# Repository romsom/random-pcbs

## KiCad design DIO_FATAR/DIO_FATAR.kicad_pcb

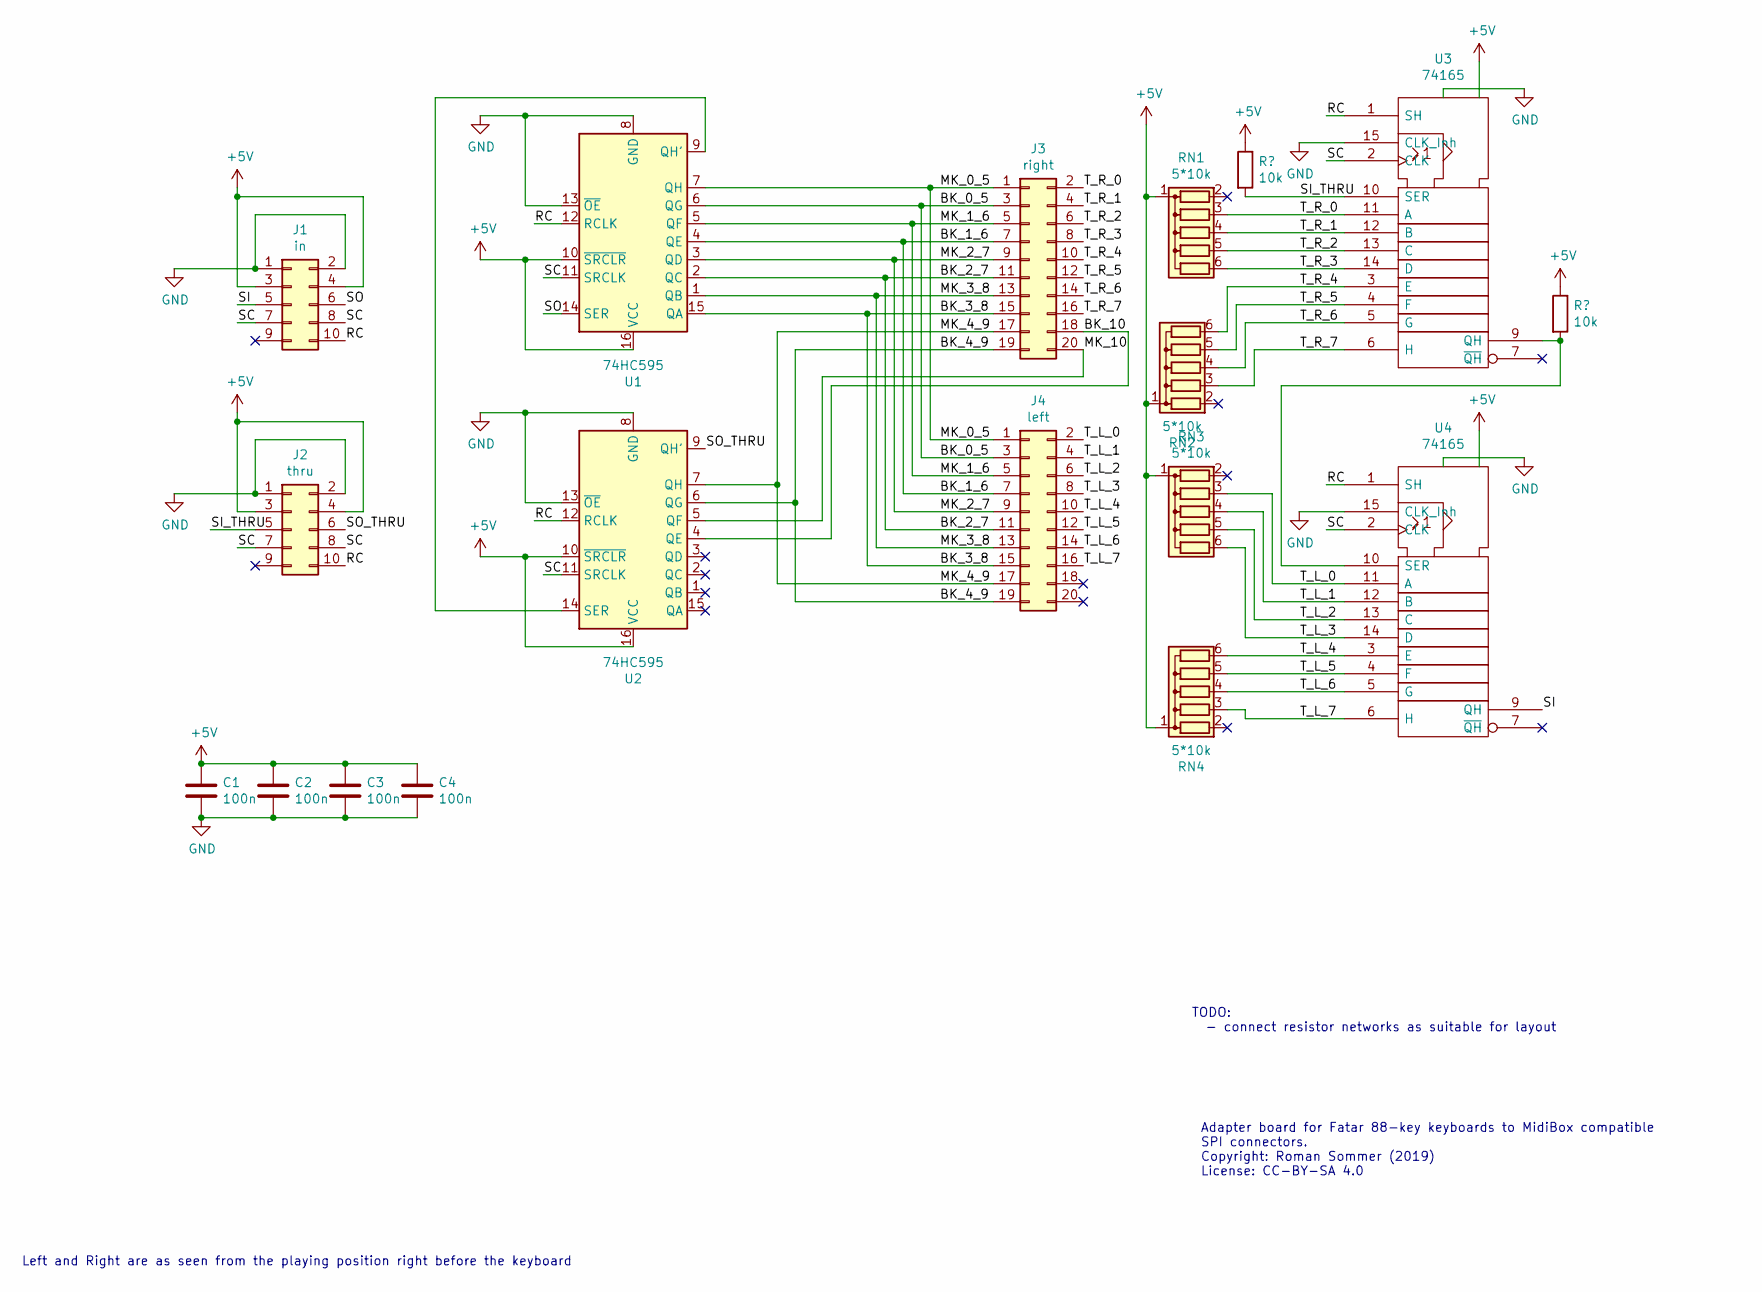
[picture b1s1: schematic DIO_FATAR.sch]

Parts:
C1, C2, C3, C4: 100n; C_Disc_D5.1mm_W3.2mm_P5.00mm
J1: in; IDC-Header_2x05_P2.54mm_Vertical
J2: thru; IDC-Header_2x05_P2.54mm_Vertical
J3: right; IDC-Header_2x10_P2.54mm_Vertical
J4: left; IDC-Header_2x10_P2.54mm_Vertical
RN1, RN2, RN3, RN4: 5*10k; R_Array_SIP6
U1, U2: 74HC595; DIP-16_W7.62mm_LongPads
U3, U4: 74165; DIP-16_W7.62mm_LongPads

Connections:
+5V: C1.1, C2.1, C3.1, C4.1, J1.3, J1.4, J2.3, J2.4, RN1.1 (common), RN2.1 (common), RN3.1 (common), RN4.1 (common), U1.10 (~SRCLR), U1.16 (VCC), U2.10 (~SRCLR), U2.16 (VCC), U3.16 (VCC), U4.16 (VCC); also elsewhere on the board
/BK_0_5: J3.3, J4.3, U1.6 (QG)
/BK_1_6: J3.7, J4.7, U1.4 (QE)
/BK_2_7: J3.11, J4.11, U1.2 (QC)
/BK_3_8: J3.15, J4.15, U1.15 (QA)
/BK_4_9: J3.19, J4.19, U2.6 (QG)
/BK_10: J3.18, U2.4 (QE)
/MK_0_5: J3.1, J4.1, U1.7 (QH)
/MK_1_6: J3.5, J4.5, U1.5 (QF)
/MK_2_7: J3.9, J4.9, U1.3 (QD)
/MK_3_8: J3.13, J4.13, U1.1 (QB)
/MK_4_9: J3.17, J4.17, U2.7 (QH)
/MK_10: J3.20, U2.5 (QF)
/RC: J1.10, J2.10, U1.12 (RCLK), U2.12 (RCLK), U3.1 (SH), U4.1 (SH)
/SC: J1.7, J1.8, J2.7, J2.8, U1.11 (SRCLK), U2.11 (SRCLK), U3.2 (CLK), U4.2 (CLK)
/SI: J1.5, U4.9 (QH)
/SI_THRU: J2.5, U3.10 (SER); also elsewhere on the board
/SO: J1.6, U1.14 (SER)
/SO_THRU: J2.6, U2.9 (QH')
/T_L_0: J4.2, RN3.3 (R2), U4.11 (A)
/T_L_1: J4.4, RN3.4 (R3), U4.12 (B)
/T_L_2: J4.6, RN3.5 (R4), U4.13 (C)
/T_L_3: J4.8, RN3.6 (R5), U4.14 (D)
/T_L_4: J4.10, RN4.6 (R5), U4.3 (E)
/T_L_5: J4.12, RN4.5 (R4), U4.4 (F)
/T_L_6: J4.14, RN4.4 (R3), U4.5 (G)
/T_L_7: J4.16, RN4.3 (R2), U4.6 (H)
/T_R_0: J3.2, RN1.3 (R2), U3.11 (A)
/T_R_1: J3.4, RN1.4 (R3), U3.12 (B)
/T_R_2: J3.6, RN1.5 (R4), U3.13 (C)
/T_R_3: J3.8, RN1.6 (R5), U3.14 (D)
/T_R_4: J3.10, RN2.6 (R5), U3.3 (E)
/T_R_5: J3.12, RN2.5 (R4), U3.4 (F)
/T_R_6: J3.14, RN2.4 (R3), U3.5 (G)
/T_R_7: J3.16, RN2.3 (R2), U3.6 (H)
GND: C1.2, C2.2, C3.2, C4.2, J1.1, J1.2, J2.1, J2.2, U1.8 (GND), U1.13 (~OE), U2.8 (GND), U2.13 (~OE), U3.8 (GND), U3.15 (CLK_Inh), U4.8 (GND), U4.15 (CLK_Inh)
unnamed 40: U3.9 (QH), U4.10 (SER); also elsewhere on the board
unnamed: U1.9 (QH'), U2.14 (SER)

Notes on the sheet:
Left and Right are as seen from the playing position right before the keyboard
Adapter board for Fatar 88-key keyboards to MidiBox compatible SPI connectors. Copyright: Roman Sommer (2019) License: CC-BY-SA 4.0
TODO: - connect resistor networks as suitable for layout

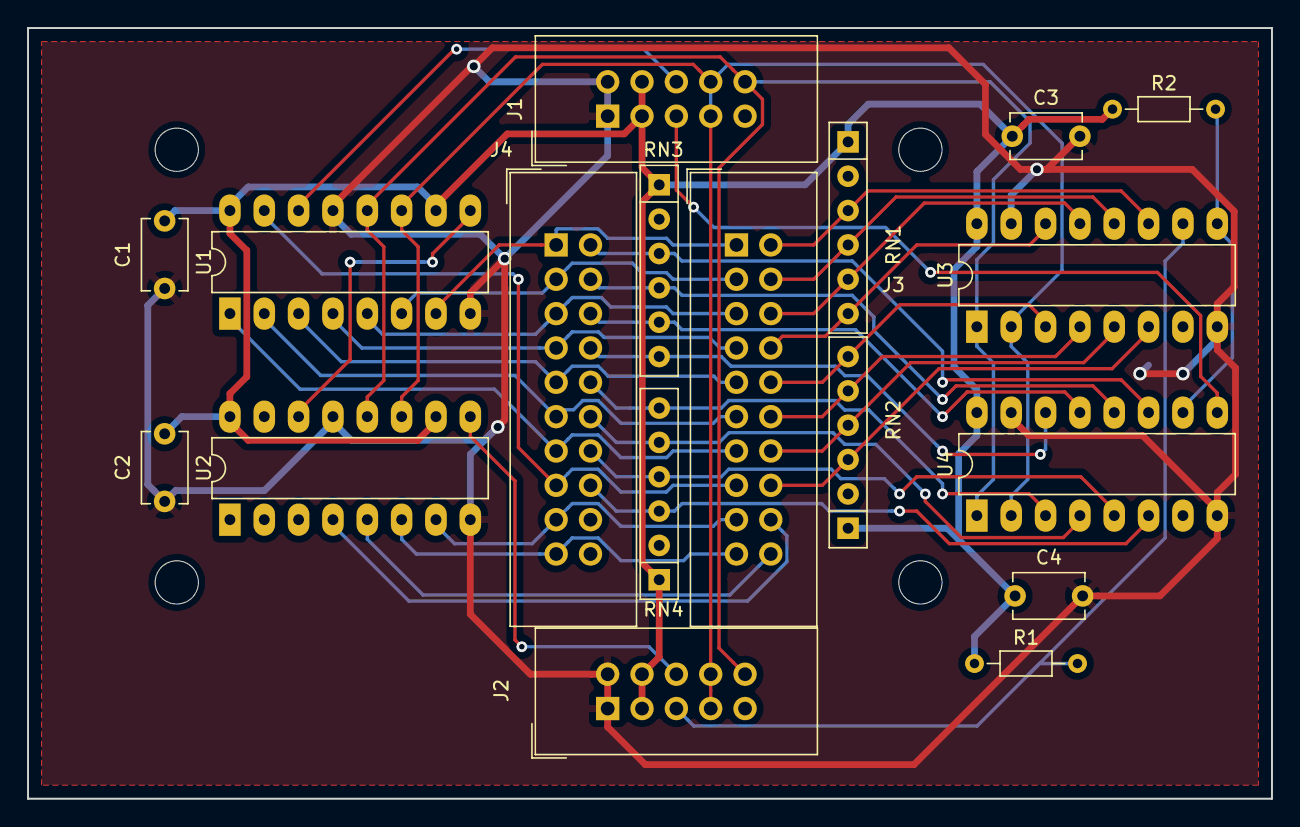
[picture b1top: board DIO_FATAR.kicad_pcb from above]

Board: 2 copper layers, 92.0 x 57.0 mm, 18 parts (0 on the bottom side), 38 nets.

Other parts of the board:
R1, R2: 10k; R_Axial_DIN0204_L3.6mm_D1.6mm_P7.62mm_Horizontal

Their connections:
+5V: R1.1, R2.1; also elsewhere on the board
/SI_THRU: R1.2; also elsewhere on the board
unnamed 40: R2.2; also elsewhere on the board

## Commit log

2019-02-13 init
2019-02-13 DIO_FATAR: schematic mostly done
2019-02-13 DIO_FATAR: add footprint annotations
2019-02-13 DIO_FATAR: use socketless footprint for DIP packages, add netlist
2019-02-13 DIO_FATAR: layout: create basic outline
2019-02-13 DIO_FATAR: remove mounting hole references
2019-02-13 DIO_FATAR: move silkscreen text / minimize overlap
2019-02-15 DIO_FATAR: route input sr
2019-02-15 DIO_FATAR: position resistor networks
2019-02-15 DIO_FATAR: move J1,2 for better clock routing
2019-06-08 DIO_FATAR: connect and roughly position resistor networks
2019-06-08 DIO_FATAR: route everything except two resistors
2019-06-08 DIO_FATAR: route remaining resistors
2019-06-08 DIO_FATAR: adjust edge cuts
2019-06-08 DIO_FATAR: finalize
    - add fills
    - adjust cuts once more
    - move R1, R2
    - move part references
2019-06-09 DIO_FATAR: add vias to fill a small empty space
2019-12-14 qc2-adapter: init, full tristate
2019-12-14 qc2-adapter: fix orientation of pnp transistors, remove logically unnecessary parts, add voltage regulator and config jumpers
2019-12-14 fix USB socket, annotate
2019-12-14 qc2-adapter: add initial footprints
2019-12-14 qc2-adapter: export netlist for veroroute
2019-12-14 qc2-adapter: edit netlist for veroroute
2019-12-15 qc2-adapter: add initial version (error in schematic!)
2019-12-15 qc2-adapter: fix only schem/netlist: add voltage dividers
